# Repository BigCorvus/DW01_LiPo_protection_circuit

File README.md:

# DW01_LiPo_protection_circuit
These are ubiquitous, but what if you want to incorporate them into your own designs?

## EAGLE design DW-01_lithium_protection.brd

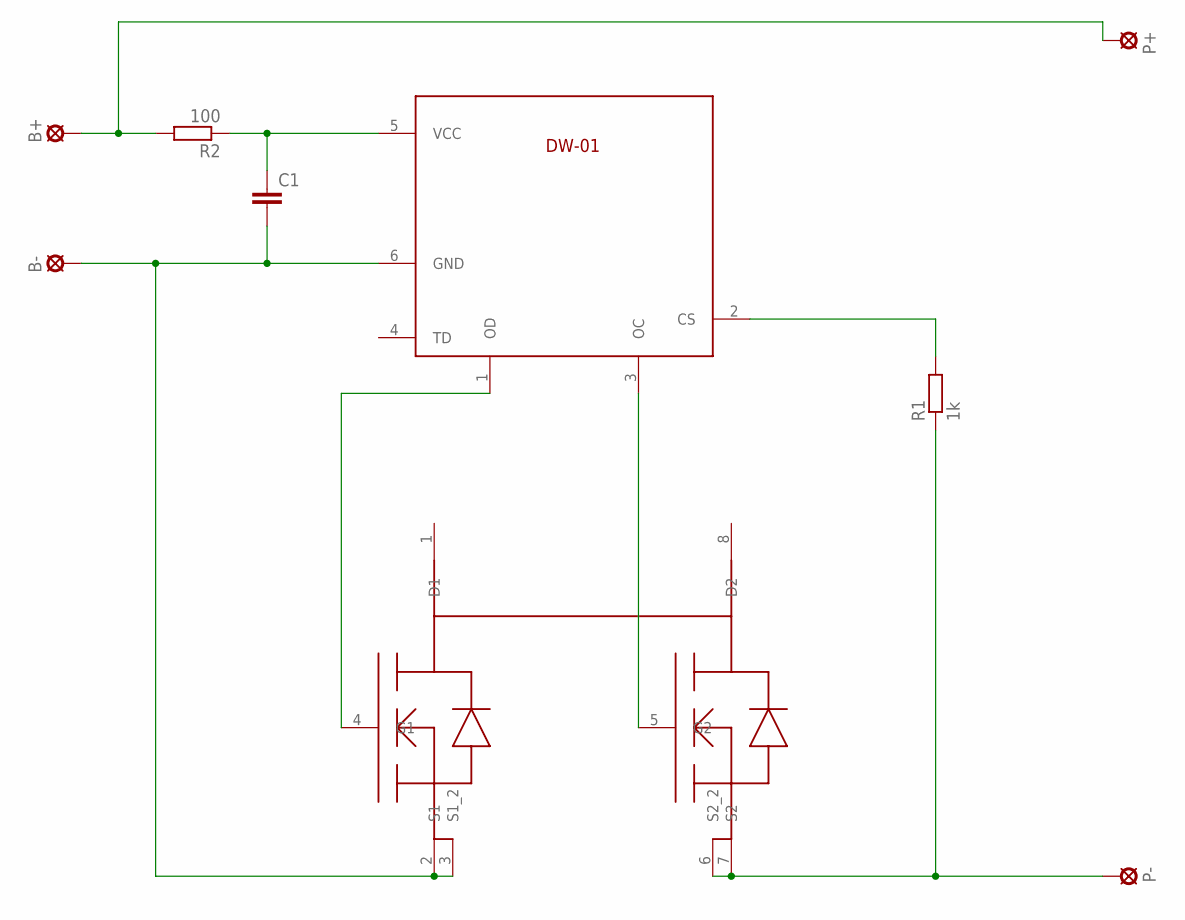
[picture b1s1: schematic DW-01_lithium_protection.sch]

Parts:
B+: LSP10
B-: LSP10
C1: C-EUC0603; C0603
P+: LSP10
P-: LSP10
R1: 1k; R0603
R2: 100; R0603
U$1: DW-01; SOT23-6
U$2: 8205A; TSSOP8

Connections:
unnamed: U$1.1 (OD), U$2.4 (G1)
unnamed: U$1.3 (OC), U$2.5 (G2)
unnamed: C1.1, R2.1, U$1.5 (VCC)
unnamed: R1.2, U$1.2 (CS)
unnamed: P-.MP, R1.1, U$2.6 (S2_2), U$2.7 (S2)
unnamed: B-.MP, C1.2, U$1.6 (GND), U$2.2 (S1), U$2.3 (S1_2)
unnamed: B+.MP, P+.MP, R2.2

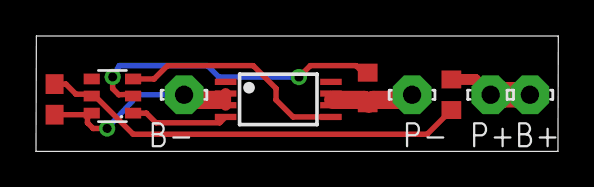
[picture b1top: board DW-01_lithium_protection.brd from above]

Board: 2 copper layers, 29.0 x 6.4 mm, 9 parts (0 on the bottom side), 7 nets.
